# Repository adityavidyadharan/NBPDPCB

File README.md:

# NBPDPCB

PCB Layout and Multisim for NBPD Lighting Project

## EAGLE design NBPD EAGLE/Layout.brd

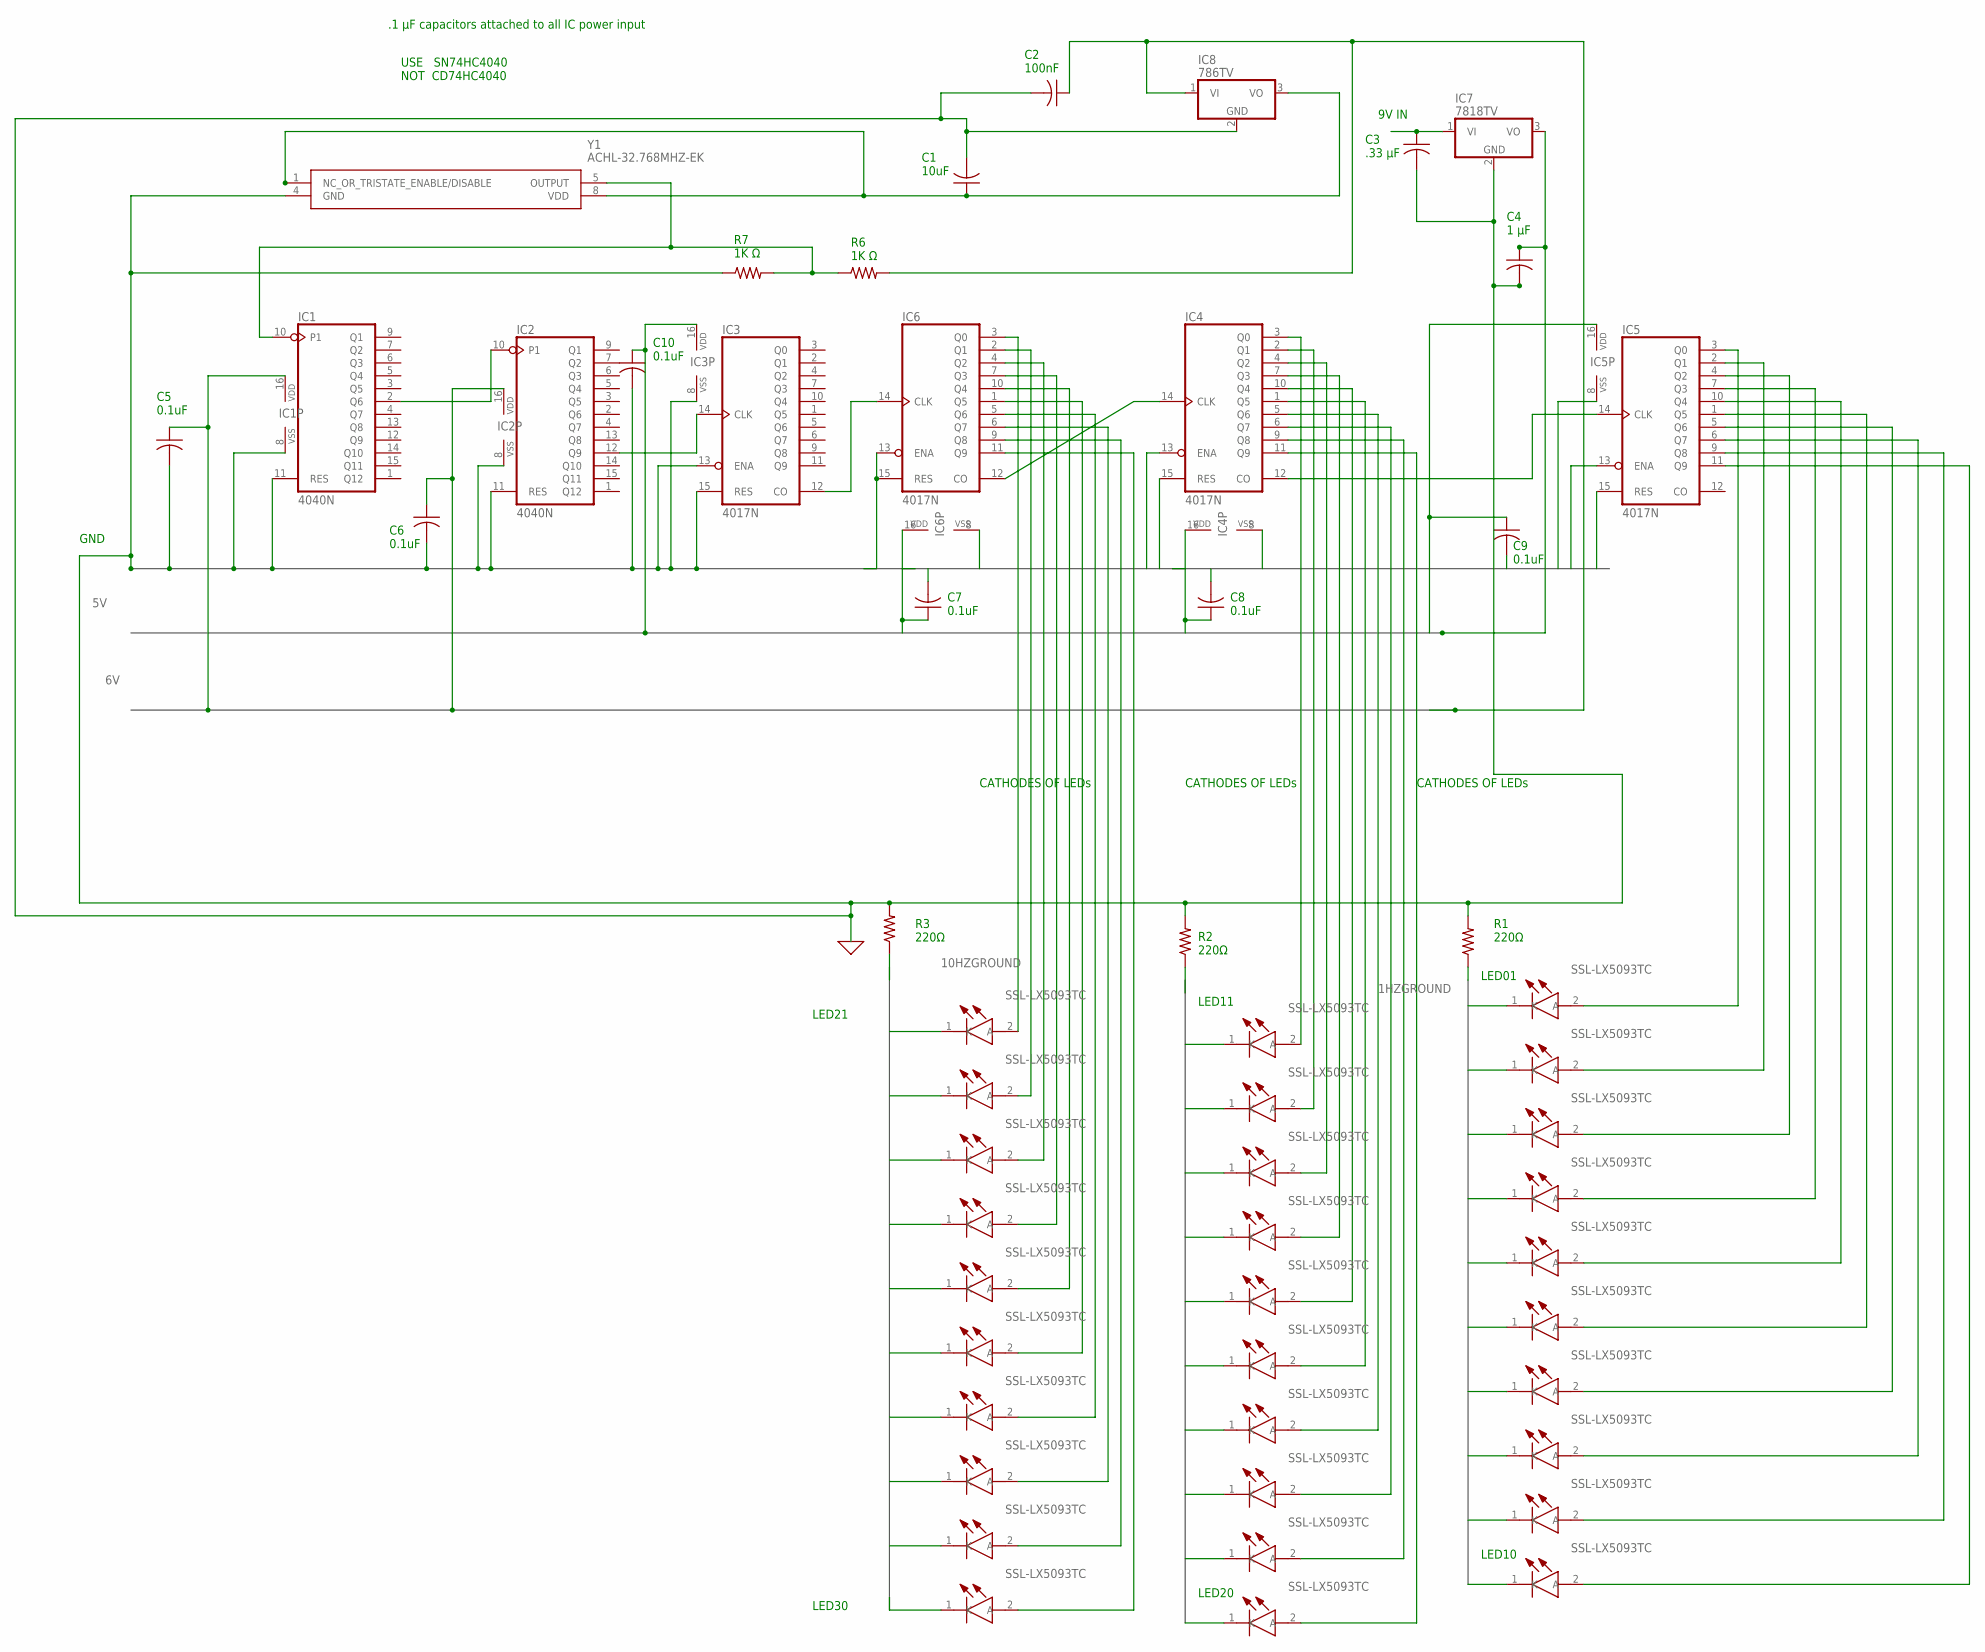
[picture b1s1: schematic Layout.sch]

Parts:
C1, C4: 1uF; C075-063X106
C2: .33uF; C075-063X106
C3: 0.33uF; C075-063X106
C5, C6, C7, C8, C9, C10: .1uF; C075-063X106
IC1, IC2: 4040N; DIL16
IC3, IC4, IC5, IC6: 4017N; DIL16
IC7: 7818TV; TO220V
IC8: 786TV; TO220V
LED1, LED2, LED3, LED4, LED5, LED6, LED7, LED8, LED9, LED10, LED11, LED12, LED13, LED14, LED15, LED16, LED17, LED18, LED19, LED20, LED21, LED22, LED23, LED24, LED25, LED26, LED27, LED28, LED29, LED30: SSL-LX5093TC; SSL-LX5093SGC/B
R1, R2, R3: 220; 0207/12
R6, R7: 1k; 0309/12
Y1: ACHL-32.768MHZ-EK; ACHL

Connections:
1HZGROUND: LED1.1 (K), LED2.1 (K), LED3.1 (K), LED4.1 (K), LED5.1 (K), LED6.1 (K), LED7.1 (K), LED8.1 (K), LED9.1 (K), LED10.1 (K), R1.1
3.3: C1.1, IC8.3 (VO), Y1.1 (NC_OR_TRISTATE_ENABLE/DISABLE), Y1.8 (VDD)
5V: C4.1, C7.1, C8.1, C9.1, C10.1, IC3.16 (VDD), IC4.16 (VDD), IC5.16 (VDD), IC6.16 (VDD), IC7.3 (VO)
6V: C2.1, C5.1, C6.1, IC1.16 (VDD), IC2.16 (VDD), IC8.1 (VI), R6.2
9V: C3.1, IC7.1 (VI)
10HZGROUND: LED11.1 (K), LED12.1 (K), LED13.1 (K), LED14.1 (K), LED15.1 (K), LED16.1 (K), LED17.1 (K), LED18.1 (K), LED19.1 (K), LED20.1 (K), R2.1
100HZGROUND: LED21.1 (K), LED22.1 (K), LED23.1 (K), LED24.1 (K), LED25.1 (K), LED26.1 (K), LED27.1 (K), LED28.1 (K), LED29.1 (K), LED30.1 (K), R3.1
C1: IC4.12 (CO), IC5.14 (CLK)
C1K: IC2.12 (Q9), IC3.14 (CLK)
C10: IC4.14 (CLK), IC6.12 (CO)
C32: IC1.10 (P1), R6.1, R7.2, Y1.5 (OUTPUT)
C100: IC3.12 (CO), IC6.14 (CLK)
C512: IC1.2 (Q6), IC2.10 (P1)
LED1: IC5.3 (Q0), LED1.2 (A)
LED2: IC5.2 (Q1), LED2.2 (A)
LED3: IC5.4 (Q2), LED3.2 (A)
LED4: IC5.7 (Q3), LED4.2 (A)
LED5: IC5.10 (Q4), LED5.2 (A)
LED6: IC5.1 (Q5), LED6.2 (A)
LED7: IC5.5 (Q6), LED7.2 (A)
LED8: IC5.6 (Q7), LED8.2 (A)
LED9: IC5.9 (Q8), LED9.2 (A)
LED10: IC5.11 (Q9), LED10.2 (A)
LED11: IC4.3 (Q0), LED11.2 (A)
LED12: IC4.2 (Q1), LED12.2 (A)
LED13: IC4.4 (Q2), LED13.2 (A)
LED14: IC4.7 (Q3), LED14.2 (A)
LED15: IC4.10 (Q4), LED15.2 (A)
LED16: IC4.1 (Q5), LED16.2 (A)
LED17: IC4.5 (Q6), LED17.2 (A)
LED18: IC4.6 (Q7), LED18.2 (A)
LED19: IC4.9 (Q8), LED19.2 (A)
LED20: IC4.11 (Q9), LED20.2 (A)
LED21: IC6.3 (Q0), LED21.2 (A)
LED22: IC6.2 (Q1), LED22.2 (A)
LED23: IC6.4 (Q2), LED23.2 (A)
LED24: IC6.7 (Q3), LED24.2 (A)
LED25: IC6.10 (Q4), LED25.2 (A)
LED26: IC6.1 (Q5), LED26.2 (A)
LED27: IC6.5 (Q6), LED27.2 (A)
LED28: IC6.6 (Q7), LED28.2 (A)
LED29: IC6.9 (Q8), LED29.2 (A)
LED30: IC6.11 (Q9), LED30.2 (A)
unnamed: C1.2, C2.2, C3.2, C4.2, C5.2, C6.2, C7.2, C8.2, C9.2, C10.2, IC1.8 (VSS), IC1.11 (RES), IC2.8 (VSS), IC2.11 (RES), IC3.8 (VSS), IC3.13 (ENA), IC3.15 (RES), IC4.8 (VSS), IC4.13 (ENA), IC4.15 (RES), IC5.8 (VSS), IC5.13 (ENA), IC5.15 (RES), IC6.8 (VSS), IC6.13 (ENA), IC6.15 (RES), IC7.2 (GND), IC8.2 (GND), R1.2, R2.2, R3.2, R7.1, Y1.4 (GND)

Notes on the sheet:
9V IN
GND
R7 1K Ω
R6 1K Ω
C3 .33 µF
C4 1 µF
.1 µF capacitors attached to all IC power input
CATHODES OF LEDs
USE SN74HC4040 NOT CD74HC4040
C9 0.1uF
C8 0.1uF
C7 0.1uF
C10 0.1uF
C6 0.1uF
C5 0.1uF
C2 100nF
C1 10uF
R1 220Ω
R2 220Ω
R3 220Ω
LED21
LED30
LED11
LED20
LED01
LED10

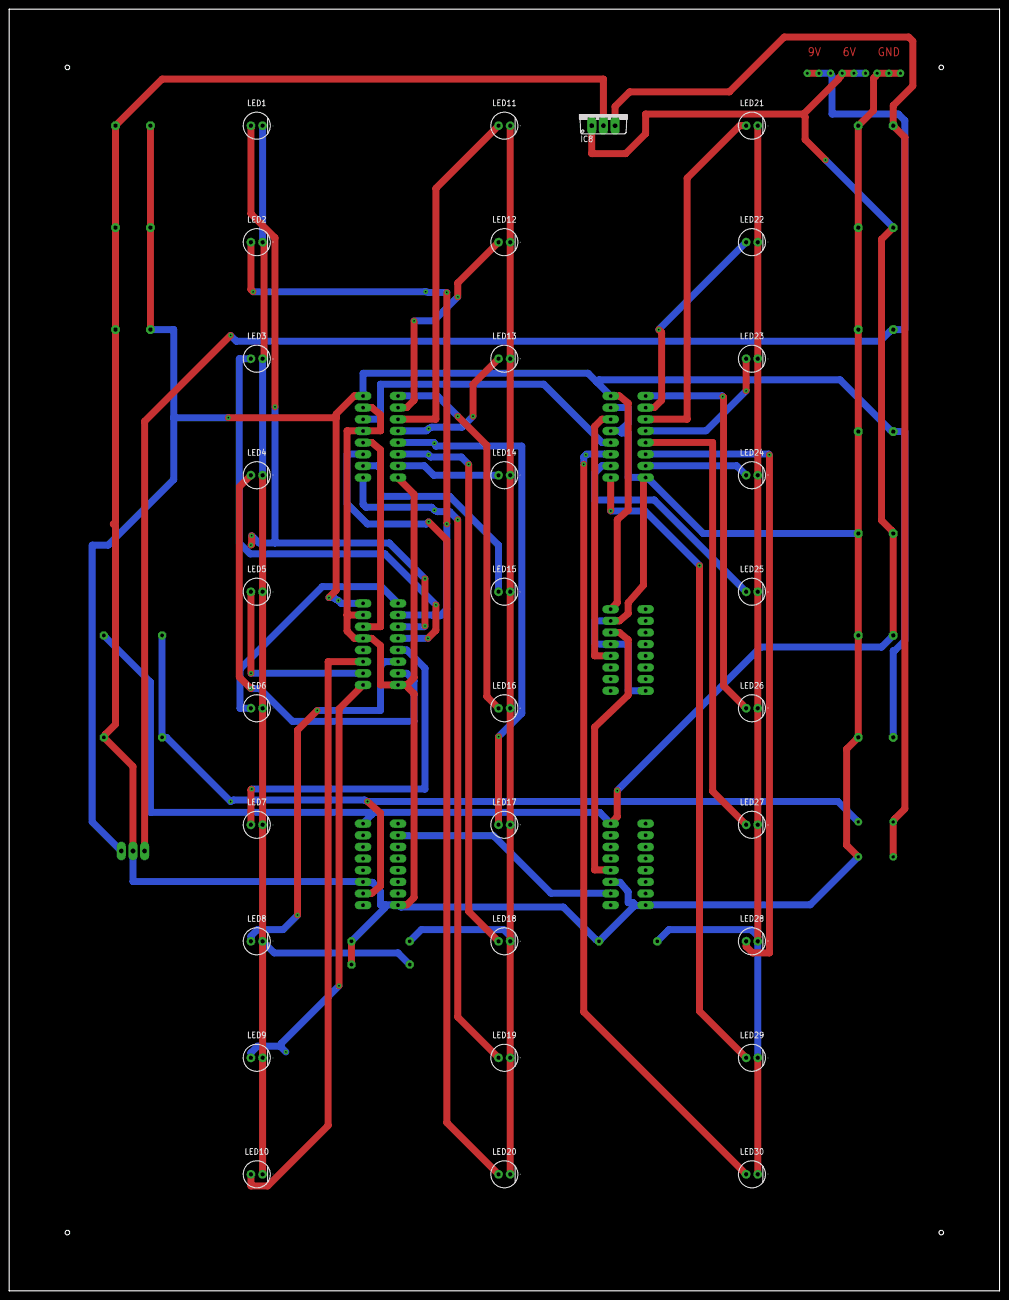
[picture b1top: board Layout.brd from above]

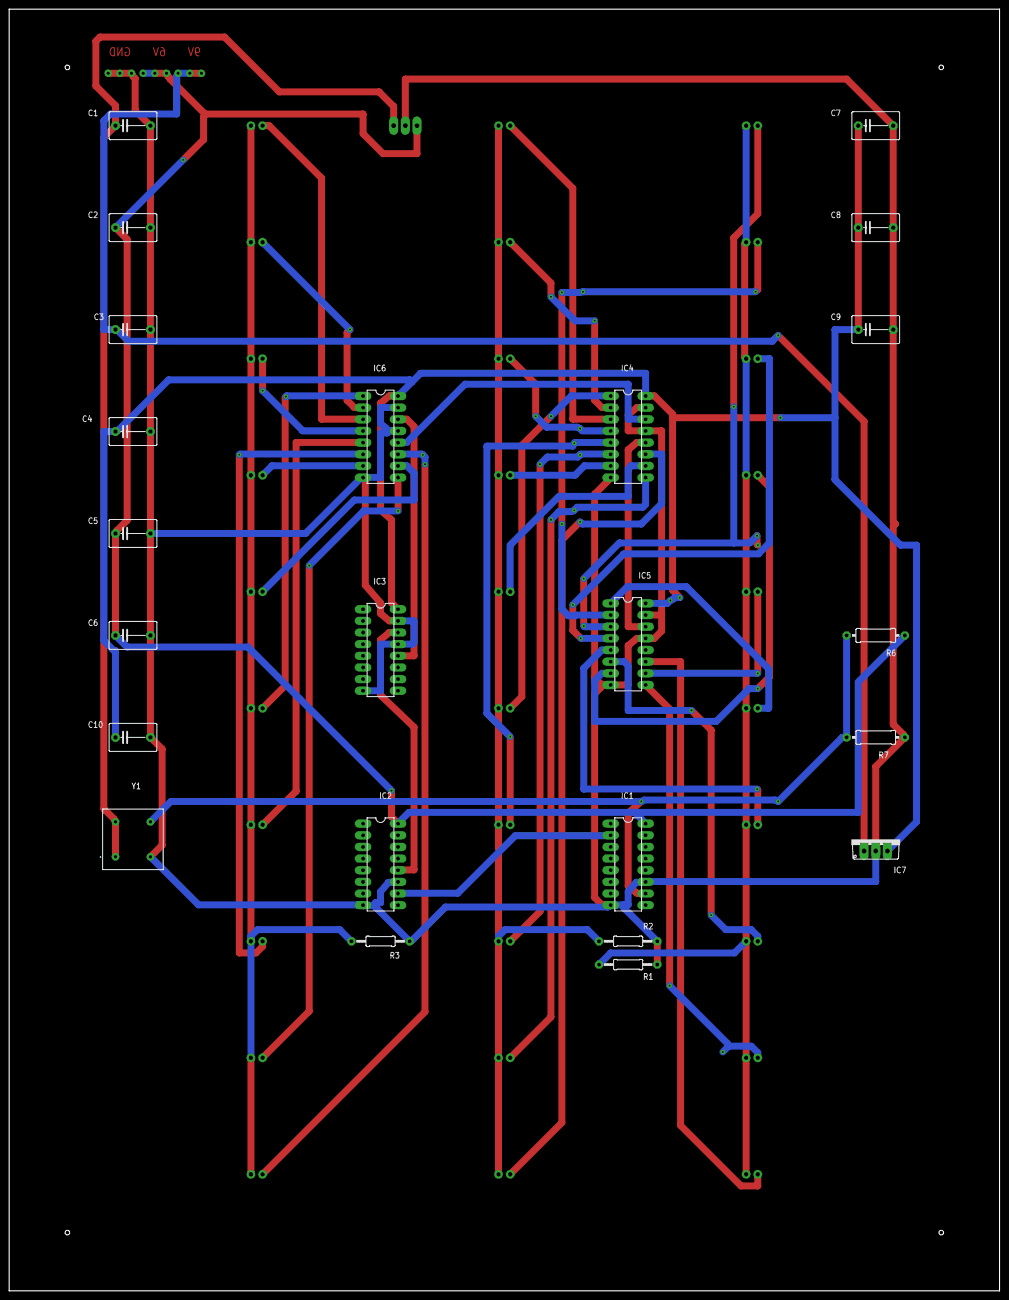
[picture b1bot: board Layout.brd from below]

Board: 2 copper layers, 215.9 x 279.4 mm, 54 parts (23 on the bottom side), 44 nets.

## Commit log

2018-12-14 Initial
2018-12-14 Add Eagle
2018-12-14 Add Chips and Osc
2018-12-15 Add Status File
2018-12-17 Add Schematic PDF
2018-12-17 Add IC connections
2018-12-17 Add LM317K
2018-12-18 Updatet
2018-12-19 Fix connection
2019-01-07 Update resistor
2019-01-11 Add text labels
2019-01-11 Update Status
2019-01-11 Updated Status
2019-01-11 Update Schematic
2019-03-14 Add labels
2019-03-14 Move Locations
2019-03-18 Test PCB
2019-03-18 10Hz 1Hz LED
2019-03-18 PCB LED UPDATE
2019-03-21 Update LED
2019-03-21 10 HZ 1 HZ
2019-03-21 Third LED
2019-03-22 Finish LED
2019-03-24 Remove Icon
2019-03-24 modified: NBPD EAGLE/Layout.s#1 modified: NBPD EAGLE/Layout.s#2 modified: NBPD EAGLE/Layout.s#3 modified: NBPD EAGLE/Layout.s#4 modified: NBPD EAGLE/Layout.s#5 modified: NBPD EAGLE/Layout.s#6 modifie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
2019-03-25 modified: NBPD EAGLE/Layout.sch
2019-03-25 PCB V1
2019-03-25 PCB PDF
2019-03-25 PCB V2
2019-03-25 Update POS
2019-04-10 PCB V4
2019-06-11 trace widen
2019-06-11 autoroute
2019-06-11 add pins
2019-06-12 final
2019-06-12 rev3 final
2019-06-18 Update PDF
2019-06-19 Schematic Labels & PDF Names
2020-01-13 3.3V Update
